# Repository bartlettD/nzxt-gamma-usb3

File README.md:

# NZXT GAMMA I/O Panel

Replacement front I/O panel for NZXT GAMMA PC case with USB 3.0 ports.

Designed in Autodesk EAGLE v 9.2

PDF Schematics and Board Images are available in the "Docs" directory.

## Features
This is essentially a slight redesign of the original I/O panel for the case.
However the original USB 2.0 ports have been replaced with USB 3.0 ports because
 I like faster transfers and 900mA current limits.

* Intel HD Audio Headphone and Line-in Jacks
* 2x USB 3.0 Ports
* eSATA connector _(Did anyone use this? Maybe replace with SD Card slot one day)_

## Does it work?
**Yes!** 

[Read my tests for USB 3.0 transfers here.](/Docs/transfer-speed-test.md)

[Read about some debug I had to go through to get Audio working properly here.](/Docs/hd-audio-debug.md)

_I didn't test eSATA because nothing uses it. Putting a USB Hub and SD Card
controller IC might be a cool upgrade for the future._

## Licence
The project is licenced under the MIT licence.

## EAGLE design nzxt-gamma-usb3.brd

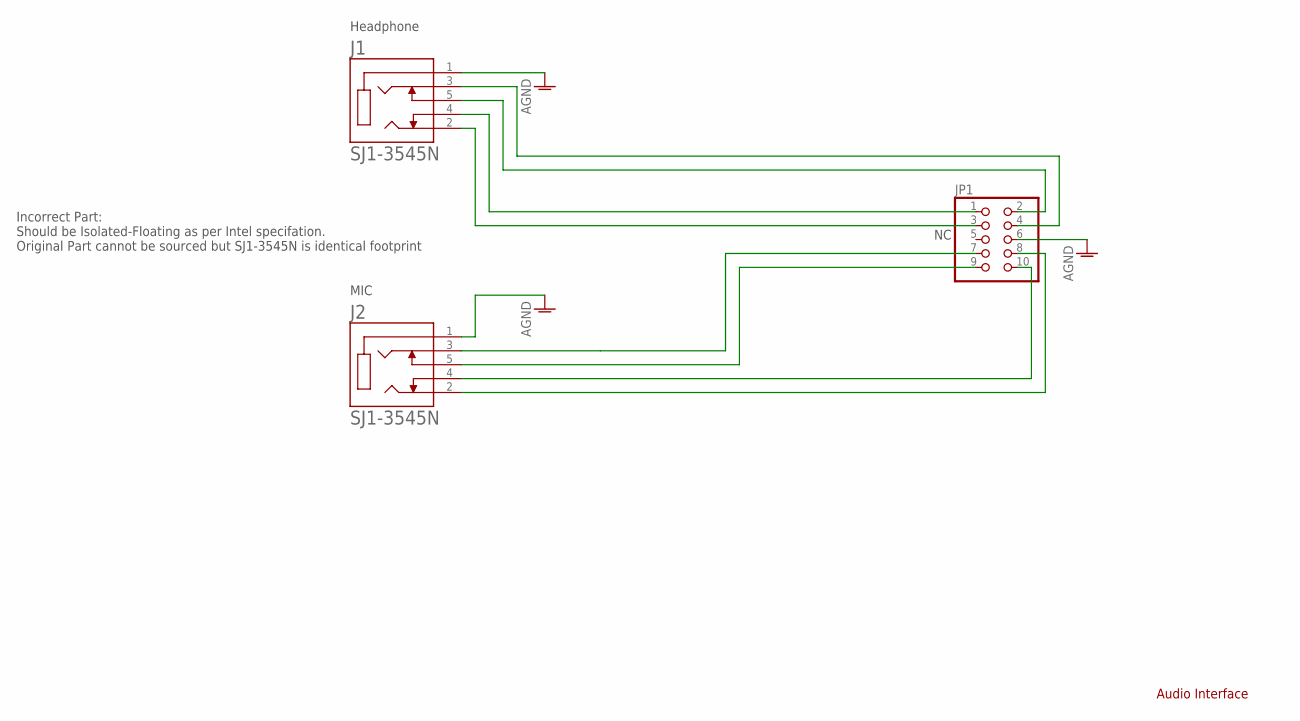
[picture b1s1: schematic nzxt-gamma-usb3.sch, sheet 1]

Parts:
J1, J2: SJ1-3545N; CUI_SJ1-3545N
JP1: PINHD-2X5; 2X05

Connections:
AGND: J1.1, J2.1, JP1.6
unnamed: J2.2, JP1.8
unnamed: J2.5, JP1.9
P_1_R: J2.3, JP1.7
P_2_L: J1.2, JP1.3
P_2_R: J1.3, JP1.4
SENSE1_1_SEND: J1.5, JP1.2
SENSE_1_RET: J2.4, JP1.10
SENSE_2_RET: J1.4, JP1.1

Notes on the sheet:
Audio Interface
Headphone
MIC
Incorrect Part: Should be Isolated-Floating as per Intel specifation. Original Part cannot be sourced but SJ1-3545N is identical footprint

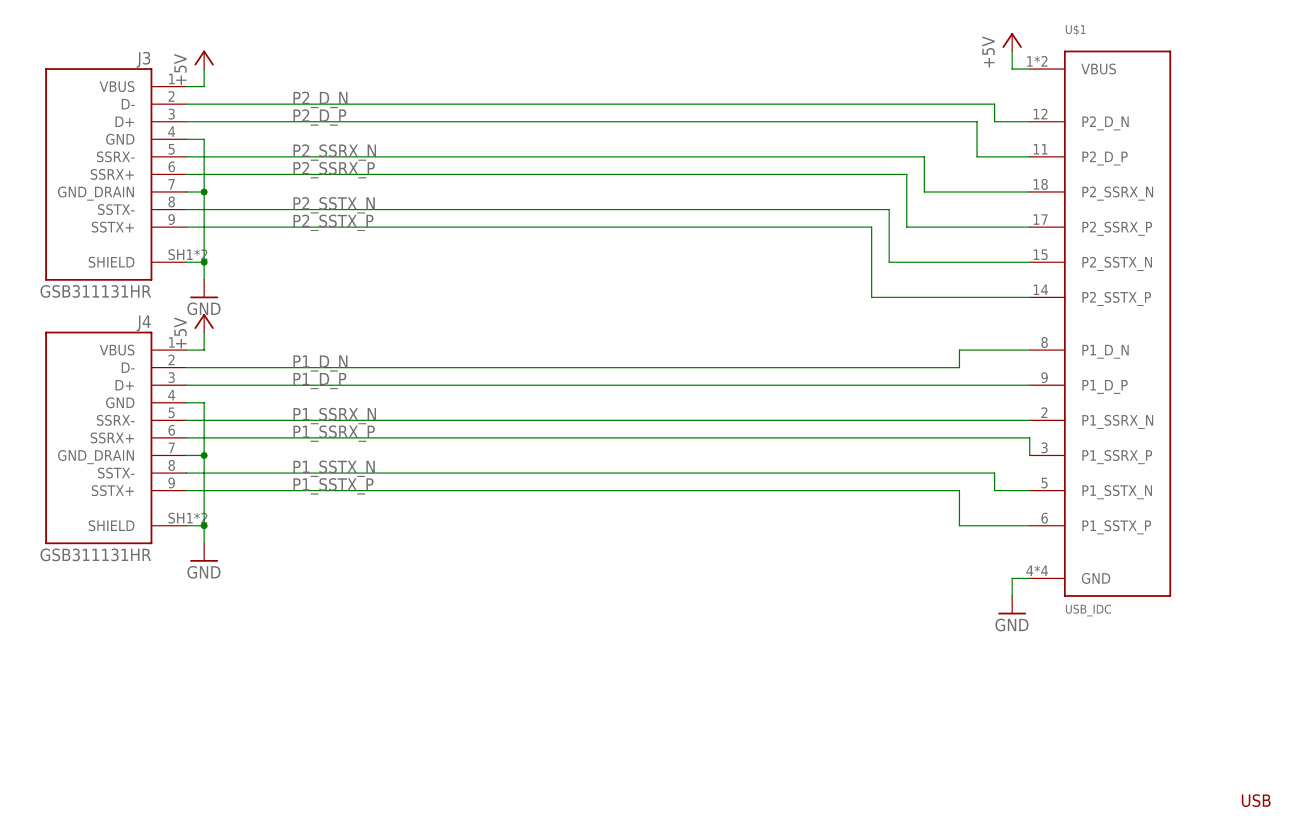
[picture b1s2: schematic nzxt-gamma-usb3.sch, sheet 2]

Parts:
J3, J4: GSB311131HR; AMPHENOL_GSB311131HR
U$1: USB_IDC; USB3_IDC

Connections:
+5V: J3.1 (VBUS), J4.1 (VBUS), U$1.1 (VBUS), U$1.19 (VBUS)
GND: J3.4 (GND), J3.7 (GND_DRAIN), J3.SH1 (SHIELD), J3.SH2 (SHIELD), J4.4 (GND), J4.7 (GND_DRAIN), J4.SH1 (SHIELD), J4.SH2 (SHIELD), U$1.4 (GND), U$1.7 (GND), U$1.13 (GND), U$1.16 (GND)
P1_D_N: J4.2 (D-), U$1.8 (P1_D_N)
P1_D_P: J4.3 (D+), U$1.9 (P1_D_P)
P1_SSRX_N: J4.5 (SSRX-), U$1.2 (P1_SSRX_N)
P1_SSRX_P: J4.6 (SSRX+), U$1.3 (P1_SSRX_P)
P1_SSTX_N: J4.8 (SSTX-), U$1.5 (P1_SSTX_N)
P1_SSTX_P: J4.9 (SSTX+), U$1.6 (P1_SSTX_P)
P2_D_N: J3.2 (D-), U$1.12 (P2_D_N)
P2_D_P: J3.3 (D+), U$1.11 (P2_D_P)
P2_SSRX_N: J3.5 (SSRX-), U$1.18 (P2_SSRX_N)
P2_SSRX_P: J3.6 (SSRX+), U$1.17 (P2_SSRX_P)
P2_SSTX_N: J3.8 (SSTX-), U$1.15 (P2_SSTX_N)
P2_SSTX_P: J3.9 (SSTX+), U$1.14 (P2_SSTX_P)

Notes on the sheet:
USB

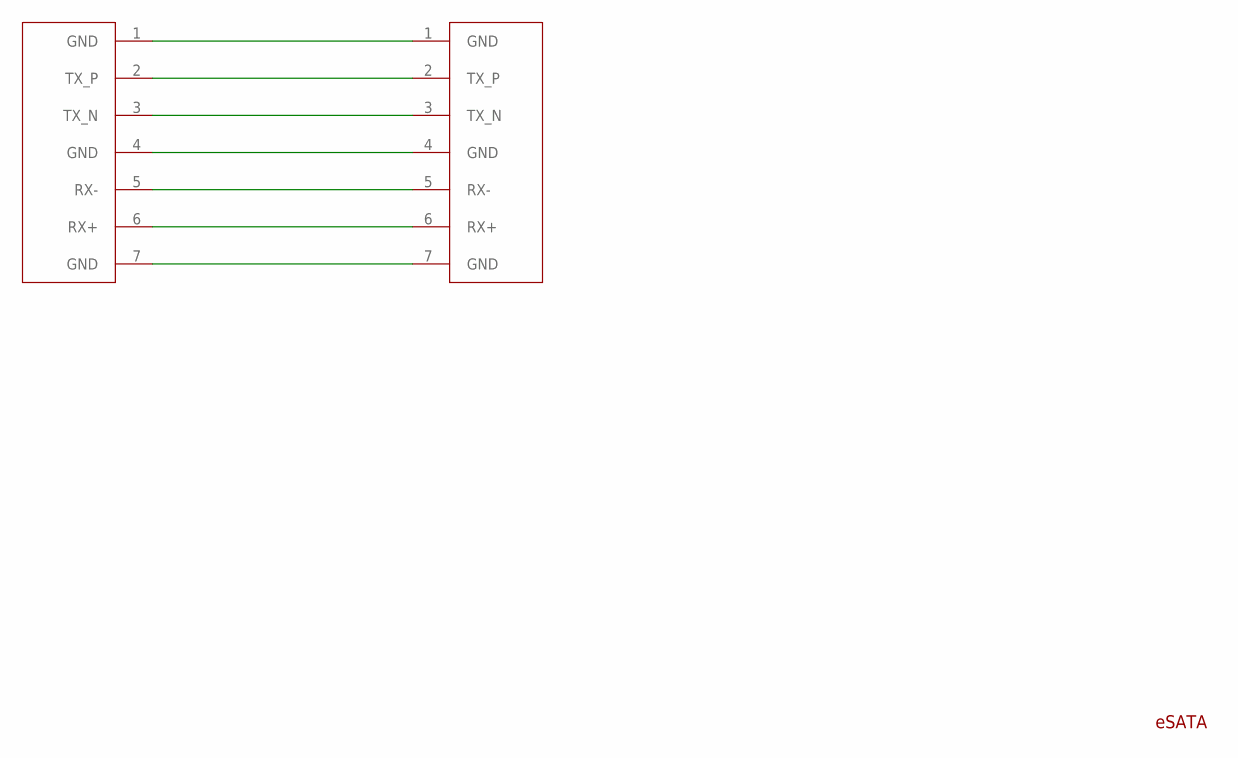
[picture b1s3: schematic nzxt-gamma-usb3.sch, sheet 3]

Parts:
U$2: G091208300LF
U$3: 0678007001

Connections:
unnamed: U$2.1 (GND), U$3.1 (GND)
unnamed: U$2.4 (GND), U$3.4 (GND)
unnamed: U$2.7 (GND), U$3.7 (GND)
unnamed: U$2.6 (RX+), U$3.6 (RX+)
unnamed: U$2.5 (RX-), U$3.5 (RX-)
unnamed: U$2.3 (TX_N), U$3.3 (TX_N)
unnamed: U$2.2 (TX_P), U$3.2 (TX_P)

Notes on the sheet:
eSATA

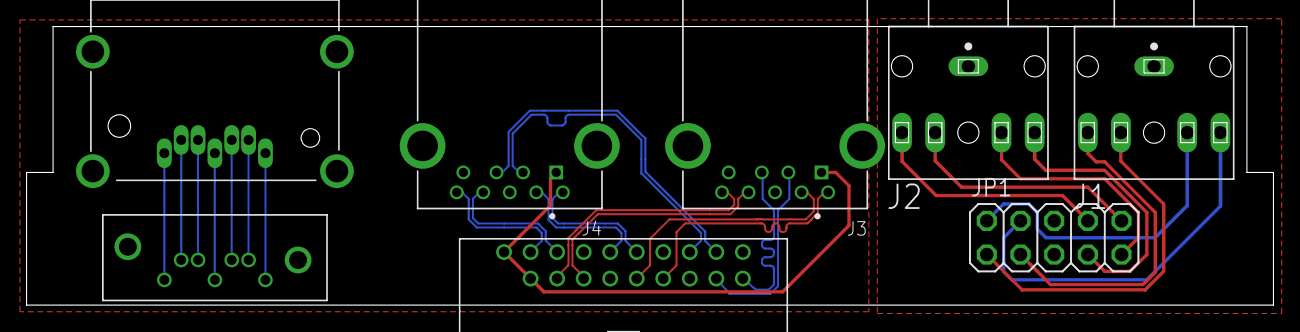
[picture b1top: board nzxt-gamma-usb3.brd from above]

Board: 2 copper layers, 94.0 x 21.0 mm, 8 parts (0 on the bottom side), 30 nets.

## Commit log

2018-09-10 Added first files
2018-09-13 Added USB 3 IDC connector
2018-10-25 Repositioned USB and eSATA ports to match casing better. started routing USB traces.
2018-10-28 Added sata connector. Length matched USB traces. Changed to managed libraries to generate 3D models.
2018-11-07 Updated components on board with better silkscreen
2018-11-09 Finished Layout
2018-11-21 Added Inter Front IO guide. Explains issue with HP jacks failing to register. Need a Normally Open connector rather than SJ1-3545N. Will steal from old board
2018-11-25 Added photos of raw and assembled boards
2018-11-25 Named some nets for debug, added some schematic detail
2018-11-26 Updated README with some project documentation.
2018-11-26 Minor styling fix
2018-11-26 Added USB 3.0 Benchmark document.
2018-11-26 Linked to Transfer benchmark page.
2018-11-26 Started writing audio debug doc. Linked to it from README
2018-11-26 Fixed wrong emoji, Petty, I know.
2018-11-26 Fixed some fonts in schematic. Exported schematics as PDF.
2018-11-26 Removed extra space in IO Guide, added screenshot to illustrate audio issue.
2018-11-26 Added some more detail to the audio-debug document.
2018-11-26 Add layout image, move image assets. Updated docs to match.
